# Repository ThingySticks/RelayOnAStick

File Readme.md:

Relay PCBs for  Particle Photon or Electron.
============================================

* BigLatchingRelay - A latching relay for low power designs.
* SimpleRelay - as the name suggests, single simple relay (Work in progress).

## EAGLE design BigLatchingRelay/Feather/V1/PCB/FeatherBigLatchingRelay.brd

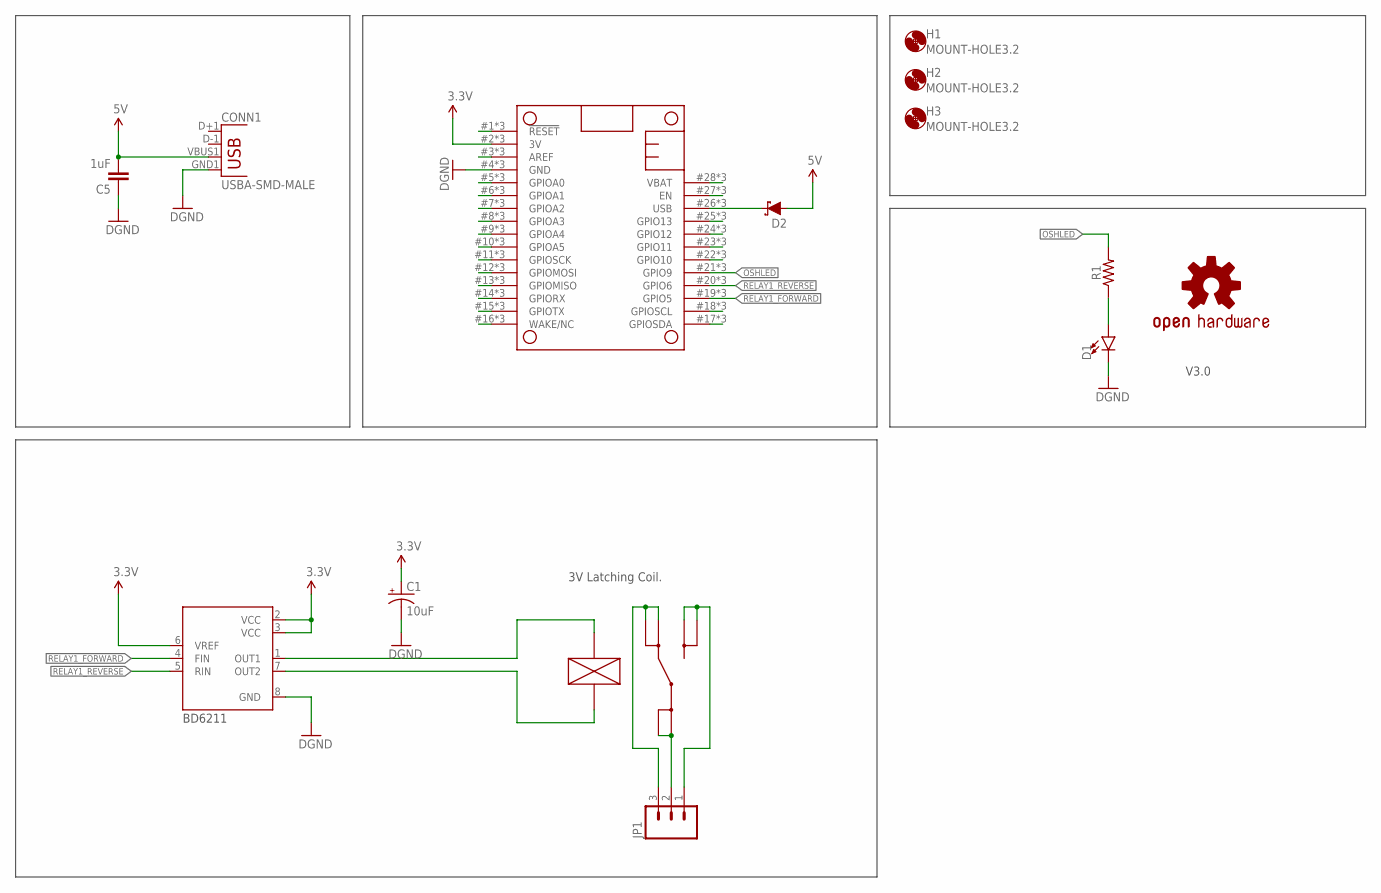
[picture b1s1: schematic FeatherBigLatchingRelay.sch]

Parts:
C1: 10uF; EIA3216
C5: 1uF; 0805
CONN1: USBA-SMD-MALE; USB-A-SMT-MALE
D1: LED1206-BOTTOM; LED-1206-BOTTOM
D2: 3A/40V/500mV; SMA-DIODE
H1, H2, H3: MOUNT-HOLE3.2; 3,2
JP1: M03-SCREW-5MM; SCREWTERMINAL-5MM-3
LOGO1: OSHW-LOGOM; OSHW-LOGO-M
MS1: FEATHERWINGFEATHERWING_BREAKOUT_INSIDEONLY; FEATHERWING_BREAKOUT_INSIDE_ONLY
R1: 1206
U3: BD6211F; SOP8
U$1: RELAY_G5RL-1E; G5RL-1E

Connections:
3.3V: C1.A (+), MS1.2 (3V), MS1.#2 (3V), MS1.@2 (3V), U3.2 (VCC), U3.3 (VCC), U3.6 (VREF)
5V: C5.2, CONN1.VBUS1 (VBUS), D2.A
GND: C1.C (-), C5.1, CONN1.GND1 (GND), D1.C, MS1.4 (GND), MS1.#4 (GND), MS1.@4 (GND), U3.8 (GND)
unnamed: JP1.2, U$1.COM@1 (COM), U$1.COM@2 (COM)
unnamed: JP1.1, U$1.NO@1 (NO), U$1.NO@2 (NO)
unnamed: JP1.3, U$1.NC@1 (NC), U$1.NC@2 (NC)
unnamed: D1.A, R1.1
unnamed: U3.1 (OUT1), U$1.COIL+
unnamed: U3.7 (OUT2), U$1.COIL-
unnamed: MS1.22 (GPIO10), MS1.#22 (GPIO10), MS1.@22 (GPIO10)
unnamed: MS1.23 (GPIO11), MS1.#23 (GPIO11), MS1.@23 (GPIO11)
unnamed: MS1.24 (GPIO12), MS1.#24 (GPIO12), MS1.@24 (GPIO12)
unnamed: MS1.25 (GPIO13), MS1.#25 (GPIO13), MS1.@25 (GPIO13)
unnamed: MS1.27 (EN), MS1.#27 (EN), MS1.@27 (EN)
unnamed: MS1.1 (!RESET), MS1.#1 (!RESET), MS1.@1 (!RESET)
unnamed: MS1.3 (AREF), MS1.#3 (AREF), MS1.@3 (AREF)
unnamed: MS1.5 (GPIOA0), MS1.#5 (GPIOA0), MS1.@5 (GPIOA0)
unnamed: MS1.6 (GPIOA1), MS1.#6 (GPIOA1), MS1.@6 (GPIOA1)
unnamed: MS1.7 (GPIOA2), MS1.#7 (GPIOA2), MS1.@7 (GPIOA2)
unnamed: MS1.8 (GPIOA3), MS1.#8 (GPIOA3), MS1.@8 (GPIOA3)
unnamed: MS1.9 (GPIOA4), MS1.#9 (GPIOA4), MS1.@9 (GPIOA4)
unnamed: MS1.10 (GPIOA5), MS1.#10 (GPIOA5), MS1.@10 (GPIOA5)
unnamed: MS1.11 (GPIOSCK), MS1.#11 (GPIOSCK), MS1.@11 (GPIOSCK)
unnamed: MS1.12 (GPIOMOSI), MS1.#12 (GPIOMOSI), MS1.@12 (GPIOMOSI)
unnamed: MS1.13 (GPIOMISO), MS1.#13 (GPIOMISO), MS1.@13 (GPIOMISO)
unnamed: MS1.14 (GPIORX), MS1.#14 (GPIORX), MS1.@14 (GPIORX)
unnamed: MS1.15 (GPIOTX), MS1.#15 (GPIOTX), MS1.@15 (GPIOTX)
unnamed: MS1.16 (WAKE/NC), MS1.#16 (WAKE/NC), MS1.@16 (WAKE/NC)
unnamed: MS1.17 (GPIOSDA), MS1.#17 (GPIOSDA), MS1.@17 (GPIOSDA)
unnamed: MS1.18 (GPIOSCL), MS1.#18 (GPIOSCL), MS1.@!8 (GPIOSCL)
OSHLED: MS1.21 (GPIO9), MS1.#21 (GPIO9), MS1.@21 (GPIO9), R1.2
RELAY1_FORWARD: MS1.19 (GPIO5), MS1.#19 (GPIO5), MS1.@19 (GPIO5), U3.4 (FIN)
RELAY1_REVERSE: MS1.20 (GPIO6), MS1.#20 (GPIO6), MS1.@20 (GPIO6), U3.5 (RIN)
USB: D2.C, MS1.26 (USB), MS1.#26 (USB), MS1.@26 (USB)
VBAT: MS1.28 (VBAT), MS1.#28 (VBAT), MS1.@28 (VBAT)

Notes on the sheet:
3V Latching Coil.
BD6211
V3.0

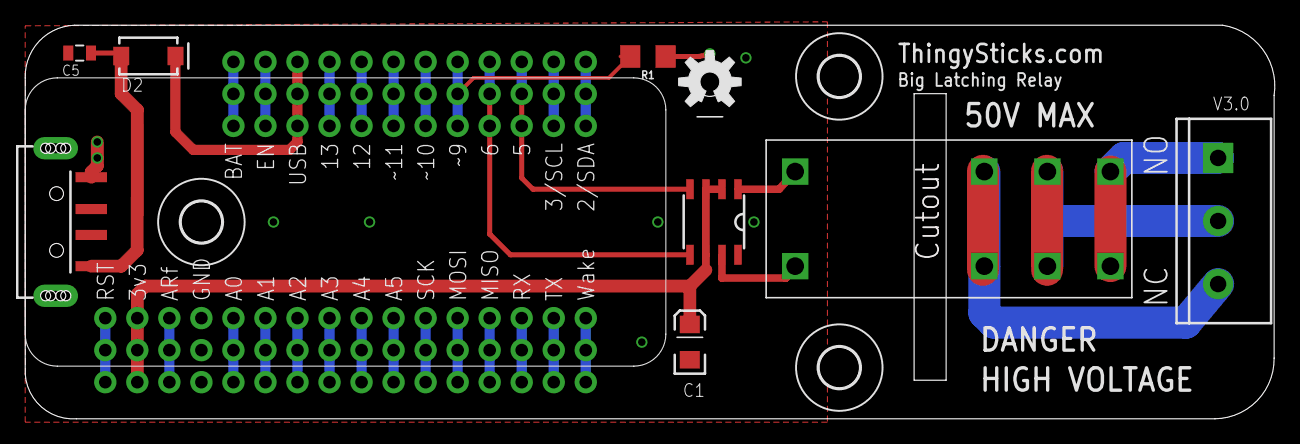
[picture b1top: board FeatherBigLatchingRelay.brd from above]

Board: 2 copper layers, 99.1 x 31.2 mm, 14 parts (1 on the bottom side), 35 nets.

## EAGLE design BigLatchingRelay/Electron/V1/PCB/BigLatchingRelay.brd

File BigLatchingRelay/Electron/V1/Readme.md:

Big Latching Relay - For Particle Photon or Electron.
=====================================================

Simple single lathcing power relay PCB. 

Suitable for Particle Photon or Electron.

Features:
---------
* 250V AC, 24V DC 16A Relay (Don't use full current with the PCB as the tracks are not up to that!)
* Latching relay. Does not require power to stay in desired state.
* 3V DC relay, can be powered when Photon or Electron are on battery power.
* USB power in via A Connector on left edge, USB B Connector on Photon/Electron. (Do not connect both at once).
* 3 Mounting holes to allow board to be mounted in case for final use.

Mounting:
---------
Single hole middle PCB (at 14, 15.8)
Double holes end PCB (at 64.5,4 & 64.5,4)

Size:
-----
Length: 99mm
Width: 31.3mm

Parts:
------
Relay: G5RLU1EDC3, Farnell #2432863
IC2: DB6211F, Farnell: #1716259
C1: 10uF Tant Case A, Farnell: #1457413

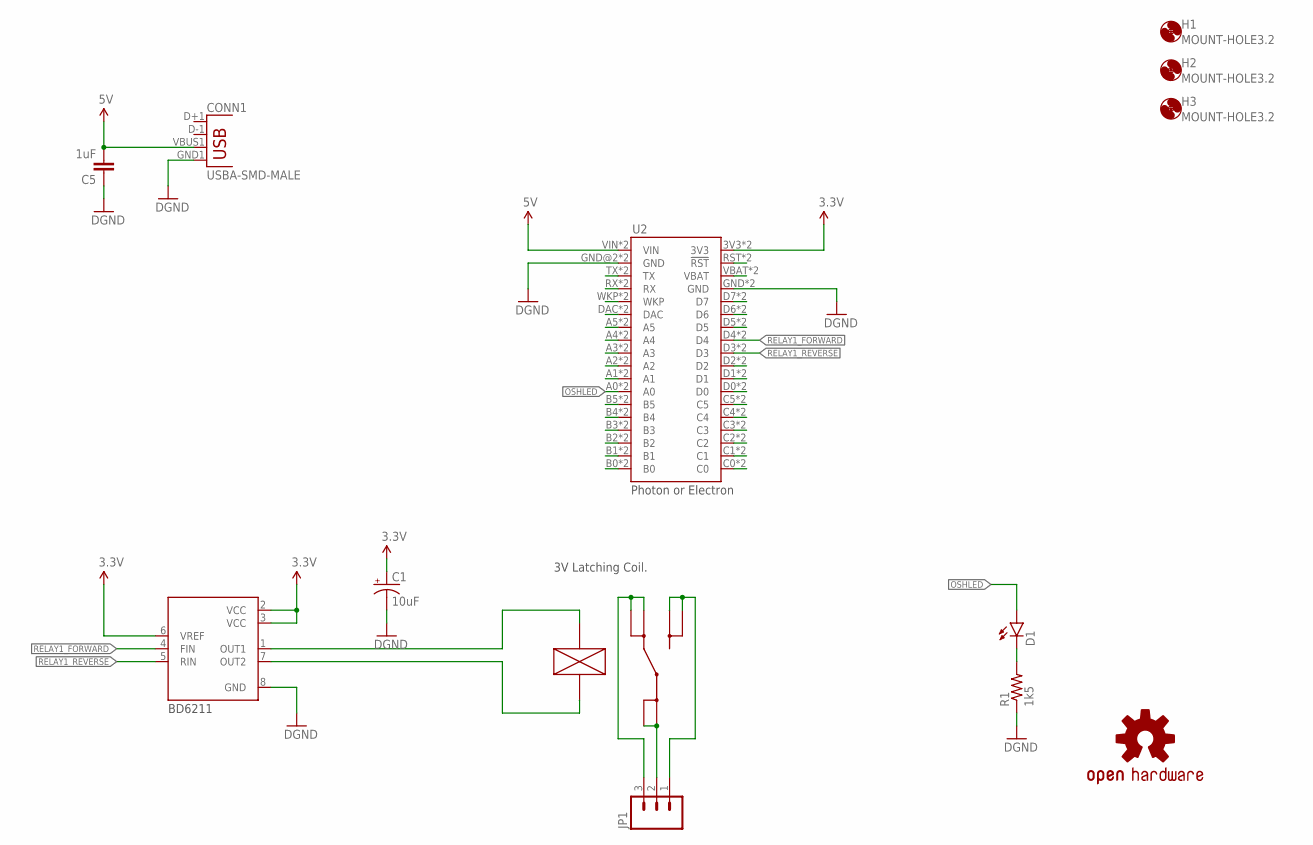
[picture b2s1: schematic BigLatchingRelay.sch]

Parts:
C1: 10uF; EIA3216
C5: 1uF; 0805
CONN1: USBA-SMD-MALE; USB-A-SMT-MALE
D1: LED1206-BOTTOM; LED-1206-BOTTOM
H1, H2, H3: MOUNT-HOLE3.2; 3,2
JP1: M03-SCREW-5MM; SCREWTERMINAL-5MM-3
LOGO1: OSHW-LOGOM; OSHW-LOGO-M
R1: 1k5; 1206
U2: ELECTRONDUALNAMED; ELECTRON_SIMPLE_SILK_NAMES_DUAL
U3: BD6211F; SOP8
U$1: RELAY_G5RL-1E; G5RL-1E

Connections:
3.3V: C1.A (+), U2.3V3, U2.3V3_1 (3V3), U3.2 (VCC), U3.3 (VCC), U3.6 (VREF)
5V: C5.2, CONN1.VBUS1 (VBUS), U2.VIN, U2.VIN_1B (VIN)
GND: C1.C (-), C5.1, CONN1.GND1 (GND), R1.1, U2.GND, U2.GND@2 (GND), U2.GND_1 (GND), U2.GND_1B (GND), U3.8 (GND)
unnamed: JP1.2, U$1.COM@1 (COM), U$1.COM@2 (COM)
unnamed: JP1.1, U$1.NO@1 (NO), U$1.NO@2 (NO)
unnamed: JP1.3, U$1.NC@1 (NC), U$1.NC@2 (NC)
unnamed: U2.VBAT, U2.VBATT_1 (VBAT)
unnamed: U2.RST (!RST), U2.RST_1 (!RST)
unnamed: D1.C, R1.2
unnamed: U3.1 (OUT1), U$1.COIL+
unnamed: U3.7 (OUT2), U$1.COIL-
unnamed: U2.D6, U2.D6_1 (D6)
unnamed: U2.D5, U2.D5_1 (D5)
unnamed: U2.D2, U2.D2_1 (D2)
unnamed: U2.D1, U2.D1_1 (D1)
unnamed: U2.D0, U2.D0_1 (D0)
unnamed: U2.C5, U2.C5_1 (C5)
unnamed: U2.C4, U2.C4_1 (C4)
unnamed: U2.C3, U2.C3_1 (C3)
unnamed: U2.C2, U2.C2_1 (C2)
unnamed: U2.C1, U2.C1_1 (C1)
unnamed: U2.C0, U2.C0_1 (C0)
unnamed: U2.B0, U2.B0_1 (B0)
unnamed: U2.B1, U2.B1_1 (B1)
unnamed: U2.B2, U2.B2_1 (B2)
unnamed: U2.B3, U2.B3_1 (B3)
unnamed: U2.B4, U2.B4_1 (B4)
unnamed: U2.B5, U2.B5_1 (B5)
unnamed: U2.D7, U2.D7_1 (D7)
unnamed: U2.A1, U2.A1_1 (A1)
unnamed: U2.A2, U2.A2_1 (A2)
unnamed: U2.A3, U2.A3_1 (A3)
unnamed: U2.A4, U2.A4_1 (A4)
unnamed: U2.A5, U2.A5_1 (A5)
unnamed: U2.DAC, U2.DAC_1 (DAC)
unnamed: U2.WKP, U2.WKP_1 (WKP)
unnamed: U2.RX, U2.RX_1 (RX)
unnamed: U2.TX, U2.TX_1 (TX)
OSHLED: D1.A, U2.A0, U2.A0_1 (A0)
RELAY1_FORWARD: U2.D4, U2.D4_1 (D4), U3.4 (FIN)
RELAY1_REVERSE: U2.D3, U2.D3_1 (D3), U3.5 (RIN)

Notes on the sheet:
3V Latching Coil.
BD6211
Photon or Electron

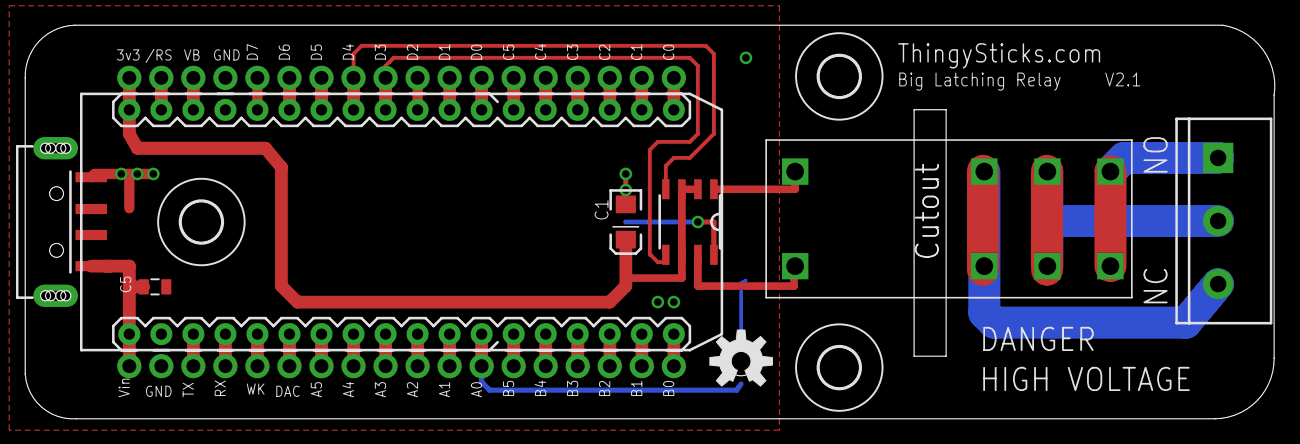
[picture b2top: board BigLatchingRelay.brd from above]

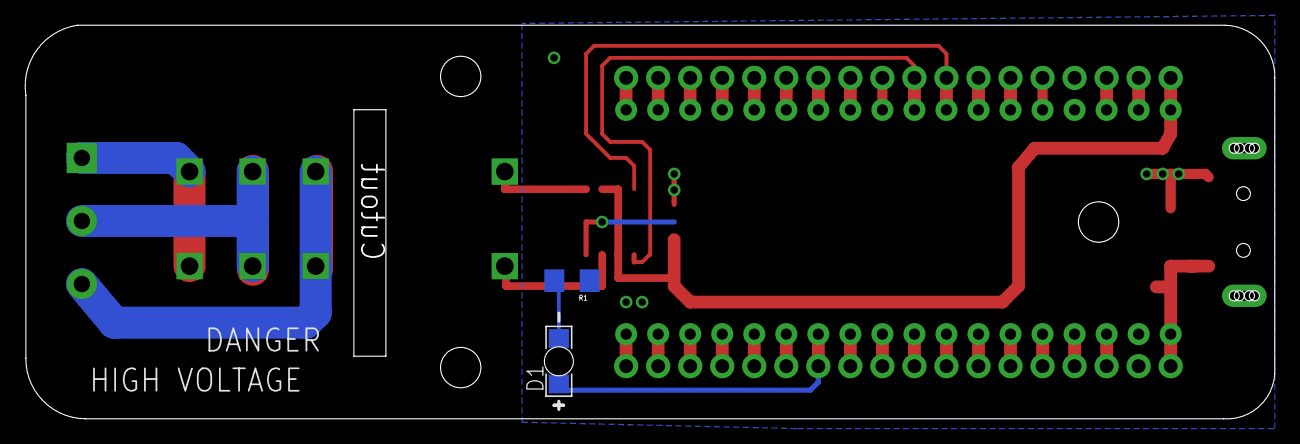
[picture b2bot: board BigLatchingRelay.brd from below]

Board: 2 copper layers, 99.1 x 31.2 mm, 13 parts (2 on the bottom side), 41 nets.

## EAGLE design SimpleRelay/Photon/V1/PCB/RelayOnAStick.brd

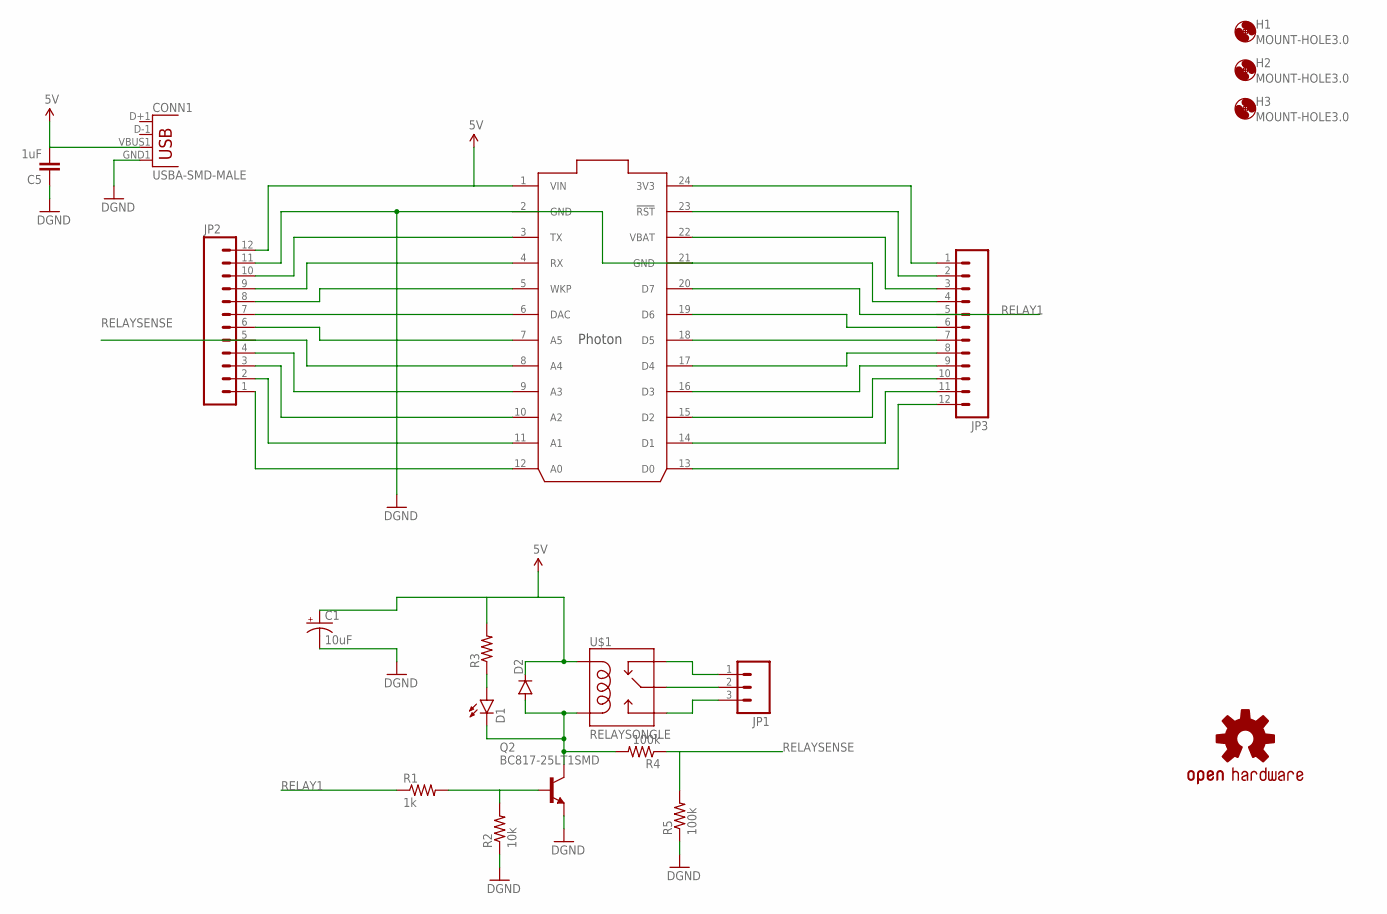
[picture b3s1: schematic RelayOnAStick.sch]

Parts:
C1: 10uF; EIA3216
C5: 1uF; 0805
CONN1: USBA-SMD-MALE; USB-A-SMT-MALE
D1: LED1206; LED-1206
D2: DIODESMA; SMA-DIODE
H1, H2, H3: MOUNT-HOLE3.0; 3,0
IC1: PHOTON
JP1: M03-SCREW-5MM; SCREWTERMINAL-5MM-3
JP2, JP3: M121X12_NO_SILK_KIT; 1X12_NO_SILK_KIT
LOGO2: OSHW-LOGOS; OSHW-LOGO-S
Q2: BC817-25LT1SMD; SOT23-BEC
R1: 1k; 1206
R2: 10k; 1206
R3: RESISTOR1206; 1206
R4, R5: 100k; 1206
U$1: RELAYSONGLE; SRD-5VDC-SL-C

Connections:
5V: C1.A (+), C5.2, CONN1.VBUS1 (VBUS), D2.C, IC1.1 (VIN), JP2.12, R3.2, U$1.COIL1
A1: IC1.11 (A1), JP2.2
GND: C1.C (-), C5.1, CONN1.GND1 (GND), IC1.2 (GND), IC1.21 (GND), JP2.11, JP3.4, Q2.E, R2.1, R5.1
unnamed: JP1.1, U$1.CLOSED (NC)
unnamed: JP1.2, U$1.COMMON (MAIN)
unnamed: JP1.3, U$1.OPEN (NO)
unnamed: IC1.24 (3V3), JP3.1
unnamed: IC1.23 (!RST), JP3.2
unnamed: IC1.22 (VBAT), JP3.3
unnamed: IC1.19 (D6), JP3.6
unnamed: IC1.18 (D5), JP3.7
unnamed: IC1.17 (D4), JP3.8
unnamed: IC1.16 (D3), JP3.9
unnamed: IC1.15 (D2), JP3.10
unnamed: IC1.14 (D1), JP3.11
unnamed: IC1.13 (D0), JP3.12
unnamed: IC1.3 (TX), JP2.10
unnamed: IC1.4 (RX), JP2.9
unnamed: IC1.5 (WKP), JP2.8
unnamed: IC1.6 (DAC), JP2.7
unnamed: IC1.7 (A5), JP2.6
unnamed: IC1.9 (A3), JP2.4
unnamed: IC1.10 (A2), JP2.3
unnamed: IC1.12 (A0), JP2.1
unnamed: D1.C, D2.A, Q2.C, R4.2, U$1.COIL2
unnamed: D1.A, R3.1
unnamed: Q2.B, R1.2, R2.2
RELAY1: IC1.20 (D7), JP3.5, R1.1
RELAYSENSE: IC1.8 (A4), JP2.5, R4.1, R5.2

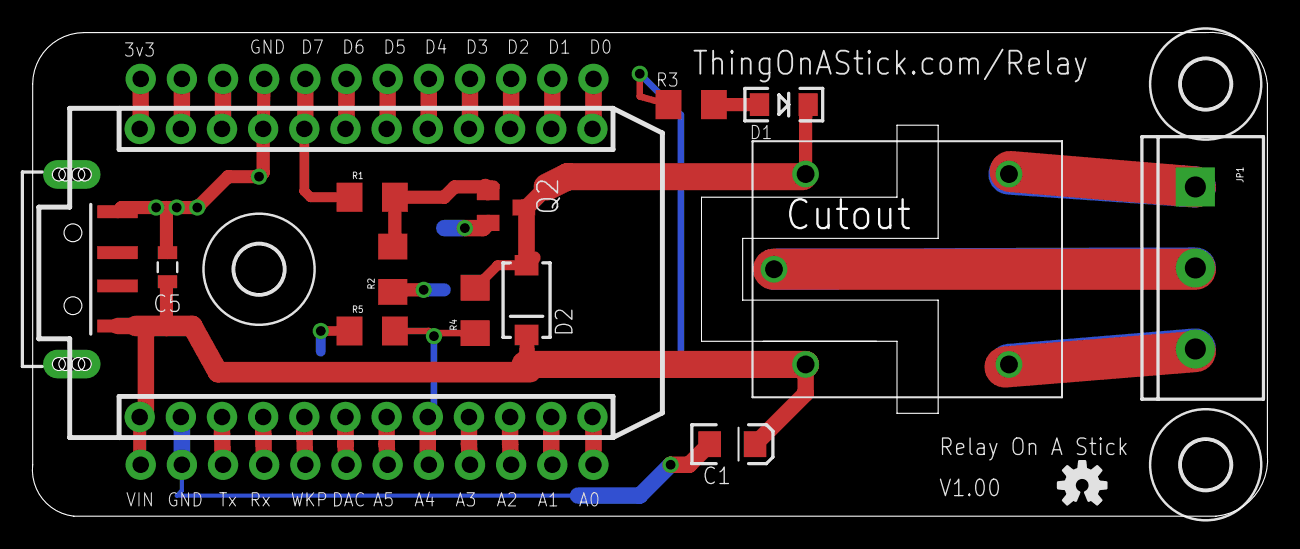
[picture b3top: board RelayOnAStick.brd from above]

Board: 2 copper layers, 76.2 x 29.9 mm, 20 parts (0 on the bottom side), 29 nets.

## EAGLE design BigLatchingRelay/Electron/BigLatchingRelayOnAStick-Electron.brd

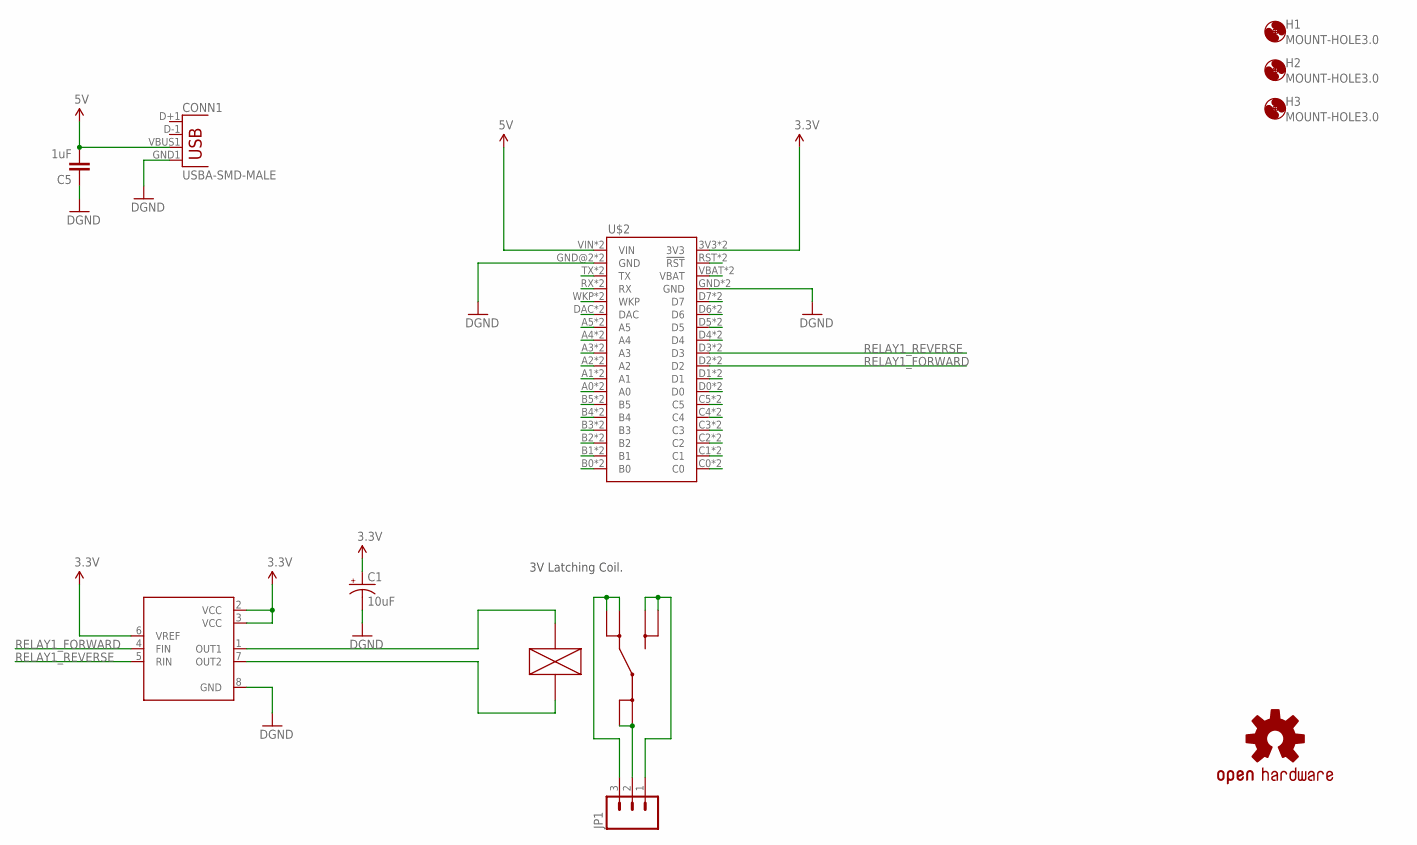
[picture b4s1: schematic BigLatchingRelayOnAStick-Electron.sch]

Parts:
C1: 10uF; EIA3216
C5: 1uF; 0805
CONN1: USBA-SMD-MALE; USB-A-SMT-MALE
H1, H2, H3: MOUNT-HOLE3.0; 3,0
IC2: BD6211F; SOP8
JP1: M03-SCREW-5MM; SCREWTERMINAL-5MM-3
LOGO2: OSHW-LOGOS; OSHW-LOGO-S
U$1: RELAY_G5RL-1E; G5RL-1E
U$2: ELECTRONDUALNAMED; ELECTRON_SIMPLE_SILK_NAMES_DUAL

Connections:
3.3V: C1.A (+), IC2.2 (VCC), IC2.3 (VCC), IC2.6 (VREF), U$2.3V3, U$2.3V3_1 (3V3)
5V: C5.2, CONN1.VBUS1 (VBUS), U$2.VIN, U$2.VIN_1B (VIN)
GND: C1.C (-), C5.1, CONN1.GND1 (GND), IC2.8 (GND), U$2.GND, U$2.GND@2 (GND), U$2.GND_1 (GND), U$2.GND_1B (GND)
unnamed: JP1.2, U$1.COM@1 (COM), U$1.COM@2 (COM)
unnamed: JP1.1, U$1.NO@1 (NO), U$1.NO@2 (NO)
unnamed: JP1.3, U$1.NC@1 (NC), U$1.NC@2 (NC)
unnamed: U$2.VBAT, U$2.VBATT_1 (VBAT)
unnamed: U$2.RST (!RST), U$2.RST_1 (!RST)
unnamed: U$2.D7, U$2.D7_1 (D7)
unnamed: IC2.1 (OUT1), U$1.COIL+
unnamed: IC2.7 (OUT2), U$1.COIL-
unnamed: U$2.D6, U$2.D6_1 (D6)
unnamed: U$2.D5, U$2.D5_1 (D5)
unnamed: U$2.D4, U$2.D4_1 (D4)
unnamed: U$2.D1, U$2.D1_1 (D1)
unnamed: U$2.D0, U$2.D0_1 (D0)
unnamed: U$2.C5, U$2.C5_1 (C5)
unnamed: U$2.C4, U$2.C4_1 (C4)
unnamed: U$2.C3, U$2.C3_1 (C3)
unnamed: U$2.C2, U$2.C2_1 (C2)
unnamed: U$2.C1, U$2.C1_1 (C1)
unnamed: U$2.C0, U$2.C0_1 (C0)
unnamed: U$2.B0, U$2.B0_1 (B0)
unnamed: U$2.B1, U$2.B1_1 (B1)
unnamed: U$2.B2, U$2.B2_1 (B2)
unnamed: U$2.B3, U$2.B3_1 (B3)
unnamed: U$2.B4, U$2.B4_1 (B4)
unnamed: U$2.B5, U$2.B5_1 (B5)
unnamed: U$2.A0, U$2.A0_1 (A0)
unnamed: U$2.A1, U$2.A1_1 (A1)
unnamed: U$2.A2, U$2.A2_1 (A2)
unnamed: U$2.A3, U$2.A3_1 (A3)
unnamed: U$2.A4, U$2.A4_1 (A4)
unnamed: U$2.A5, U$2.A5_1 (A5)
unnamed: U$2.DAC, U$2.DAC_1 (DAC)
unnamed: U$2.WKP, U$2.WKP_1 (WKP)
unnamed: U$2.RX, U$2.RX_1 (RX)
unnamed: U$2.TX, U$2.TX_1 (TX)
RELAY1_FORWARD: IC2.4 (FIN), U$2.D2, U$2.D2_1 (D2)
RELAY1_REVERSE: IC2.5 (RIN), U$2.D3, U$2.D3_1 (D3)

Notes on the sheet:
3V Latching Coil.

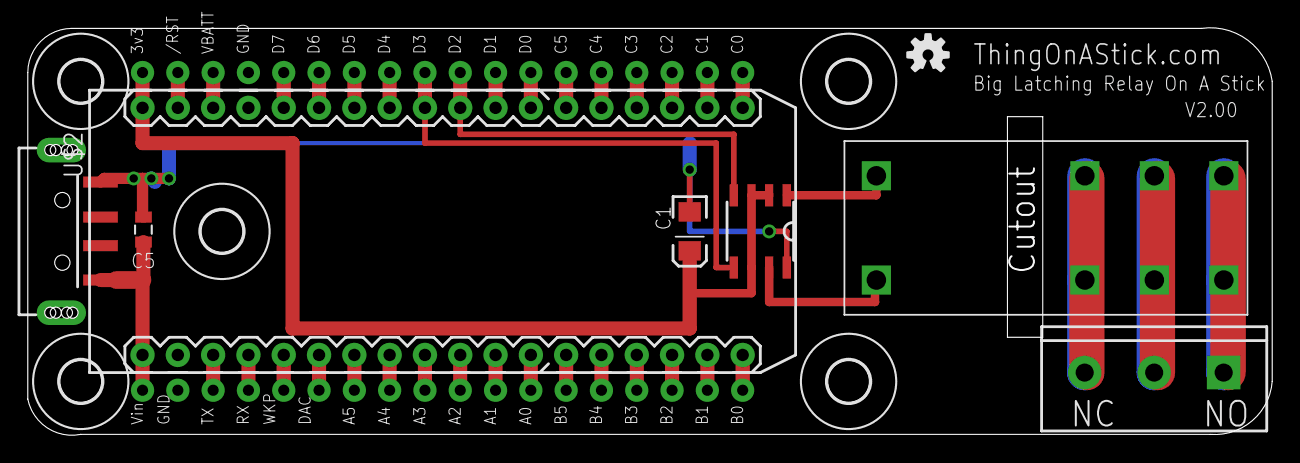
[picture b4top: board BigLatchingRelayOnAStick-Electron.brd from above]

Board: 2 copper layers, 89.5 x 29.3 mm, 13 parts (0 on the bottom side), 40 nets.

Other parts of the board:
H4, H5: MOUNT-HOLE3.0; 3,0

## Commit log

2015-12-14 Initial versions as sent to OSHPark
2015-12-14 Work in progress for case.
2016-03-29 Improved folder structure
2016-11-21 Renamed BigLatchingRelay. Updated to V2.1: Moved connector to end rather than side to reduce strain on one side when USB A connector used. Added OSH Logo LED (and bigger OSH Logo). Added high volage 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
    Added DirtyPcb images.
2016-11-21 Added readmes
2016-11-21 Added gitignore
2016-11-21 Updated parts.
2016-11-21 Added datasheets for relay and relay driver.
    Improved text on schematic.
2016-11-21 Added more dimensions to PCB.
2016-12-22 Updated part identifiers and added BOMs
2017-01-04 Fixed validation issues for bom json
2018-02-25 Feather version of the Big Latching Relay. V3 (aka rev 1) as send to DirtyPCBs

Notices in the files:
parts and their libraries:
SparkFun-Connectors: Licensing: Creative Commons ShareAlike 4.0 International - https://creativecommons.org/licenses/by-sa/4.0
